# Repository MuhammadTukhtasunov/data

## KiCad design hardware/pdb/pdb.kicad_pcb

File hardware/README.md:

# KiCad projects — Rev A

KiCad projects for the four custom boards in the
[electrical & logic design](../docs/electrical/README.md). Each one has a
complete schematic and a started PCB: board outline, mounting holes, net
classes, ground pours, and every footprint placed and grouped by circuit
block. Nothing is routed yet.

| Board | Folder | Schematic | PCB | Parts | Check results |
|-------|--------|-----------|-----|-------|---------------|
| Power Distribution Board | [`pdb/`](pdb) | [PDF](exports/pdb-schematic.pdf) (A2) | 100 × 80 mm, 4 layers · [PDF](exports/pdb-pcb.pdf) | 94 | 0 DRC violations, 189 unrouted connections |
| Jetson I/O HAT | [`hat/`](hat) | [PDF](exports/hat-schematic.pdf) (A3) | 65 × 56.5 mm, 2 layers · [PDF](exports/hat-pcb.pdf) | 38 | 0 DRC violations, 79 unrouted connections |
| Lighting Driver Board | [`lgt/`](lgt) | [PDF](exports/lgt-schematic.pdf) (A3) | 70 × 50 mm, 2 layers · [PDF](exports/lgt-pcb.pdf) | 35 | 0 DRC violations, 62 unrouted connections |
| Sensor Hub | [`sns/`](sns) | [PDF](exports/sns-schematic.pdf) (A2) | 90 × 60 mm, 2 layers · [PDF](exports/sns-pcb.pdf) | 47 | 0 DRC violations, 104 unrouted connections |

## 3D

| PDB | HAT |
|-----|-----|
|  |  |
| **LGT** | **SNS** |
|  |  |

Exported from KiCad with its 3D model library by
[`tools/export_3d.py`](tools/export_3d.py); top views are in `exports/*-3d-top.png`.
KiCad 7's library has no models for the XT60/XT30, Micro-Fit and JST-SH
connectors or the BVR shunt, so those show as plain boxes sized from their
footprints; a few chips and inductors use the closest library model. The board
files keep their original model references. In KiCad, open *View → 3D Viewer*.

## Previews

| Board | PCB (placement, unrouted) | Schematic |
|-------|---------------------------|-----------|
| PDB |  |  |
| HAT |  |  |
| LGT |  |  |
| SNS |  |  |

In the PCB images, blue is the ground fill, pink is pads and yellow is
silkscreen. Every part sits inside its outline as a starting arrangement, grouped
by circuit block; expect to rearrange them for routing.

Open the `.kicad_pro` file in **KiCad 7 or newer**. KiCad 8 and 9 upgrade the
files the first time you save.

## What's done

- **Schematics** use KiCad's standard symbols, plus a project symbol for the
  Teensy 4.1 in [`lib/drone.kicad_sym`](lib/drone.kicad_sym). Each block from
  the design doc is a labelled frame on one sheet. Every pin connects through a
  net label: global labels for nets that cross boards, using the names in
  the design doc's §3. Unused pins have no-connect flags.
- **Every pin was checked against KiCad's own netlist** (exported with
  `kicad-cli`): each pin is on the net the design intends, and no net has a
  single connection.
- **PCBs** were built from that netlist, so *Update PCB from Schematic* starts
  in sync. Every part is packed inside the outline, and each schematic block
  is a PCB group so you can select its parts together.
- **Net classes** (in each `.kicad_pro`):
  - `HighCurrent`: 3 mm track, for `PWR_VBAT` and `VBAT_RAW`.
  - `Power`: 1 mm track, for `PWR_*`, switch nodes, LED and speaker outputs, and sensor 5 V.
  - `Default`: 0.25 mm track.
  - Minimum drill is 0.2 mm, which the TI PowerPAD thermal-via footprints need.
- **Ground pours** are on `B.Cu` (and `In1.Cu` on the 4-layer PDB).
- **HAT layout:** the 40-pin socket sits along the top edge between the
  mounting holes, as on a Raspberry Pi HAT.

## Before layout: values and checks still open

Values marked **TBD** in the schematics need calculating from datasheets.
I couldn't download datasheets in the session that generated these files.

| Board | Parts | What to do |
|-------|-------|------------|
| PDB | R10–R16, C10–C13 | LM5176: EN/UVLO divider, MODE, RT (switching frequency), SLOPE, SS, compensation, FB divider for 19 V |
| PDB | L1, R17, R18, Q1–Q4 | LM5176 power stage: inductor, low-side current-sense resistor, optional output-sense resistor (0 Ω if unused), confirm CSD18540Q5B suits the chosen frequency |
| PDB | R21–R24, C23–C24, R28–R31, C31–C32, L2, L3 | TPS54560B: EN/UVLO divider, RT, compensation, inductors |
| PDB | R25/R26, R32/R33 | 52.3 k / 10 k assumes a 0.8 V feedback reference; confirm |
| PDB | J1, J2, J3 | Confirm pad 1 is + on the AMASS XT60/XT30 footprints |
| HAT | R1 (634 k) | MAX98357A SD_MODE level for (L+R)/2 mono; check the datasheet's SD_MODE table |
| HAT | U2 | Symbol is 74LVC125 (same pinout); fit a **74AHCT125** |
| LGT | R5, R11, L1, L2 | LED current (≈ 0.1 V / R) and inductor value for your emitters |
| LGT | R3/R4, R9/R10 | AL8860 CTRL voltage range and internal pull-up |
| SNS | U1 | Teensy pin numbers use DIP-48 numbering; check against the PJRC Teensy 4.1 pinout card |

Also choose the battery and motor current (shunt R1, XT60 vs XT90), and pick
final part numbers for the inductors and capacitors.

## Folder layout

```
hardware/
├── lib/drone.kicad_sym      project symbols (Teensy 4.1)
├── pdb/ hat/ lgt/ sns/      one KiCad project each (.kicad_pro, .kicad_sch, .kicad_pcb, sym-lib-table)
├── exports/                 schematic and PCB PDFs
└── tools/                   generator that bootstrapped the projects
```

## Regenerating (bootstrap only)

`tools/gen_kicad.py` holds each board's circuit as a parts-and-nets list and
writes all of the above. **It overwrites the KiCad files.** Once you start
editing in KiCad, edit the KiCad files directly and stop using the script.

It needs KiCad 7's Python module (`pcbnew`), `kiutils==1.4.8` and
`rectpack==0.2.2`:

```bash
python3 -m venv --system-site-packages .venv   # system Python that has pcbnew
.venv/bin/pip install kiutils==1.4.8 rectpack==0.2.2
.venv/bin/python hardware/tools/gen_kicad.py          # all boards
.venv/bin/python hardware/tools/gen_kicad.py lgt      # one board
```

`tools/export_3d.py <kicad 3dmodels dir> <out dir>` exports each board to VRML
with its component models (used for the 3D renders above).

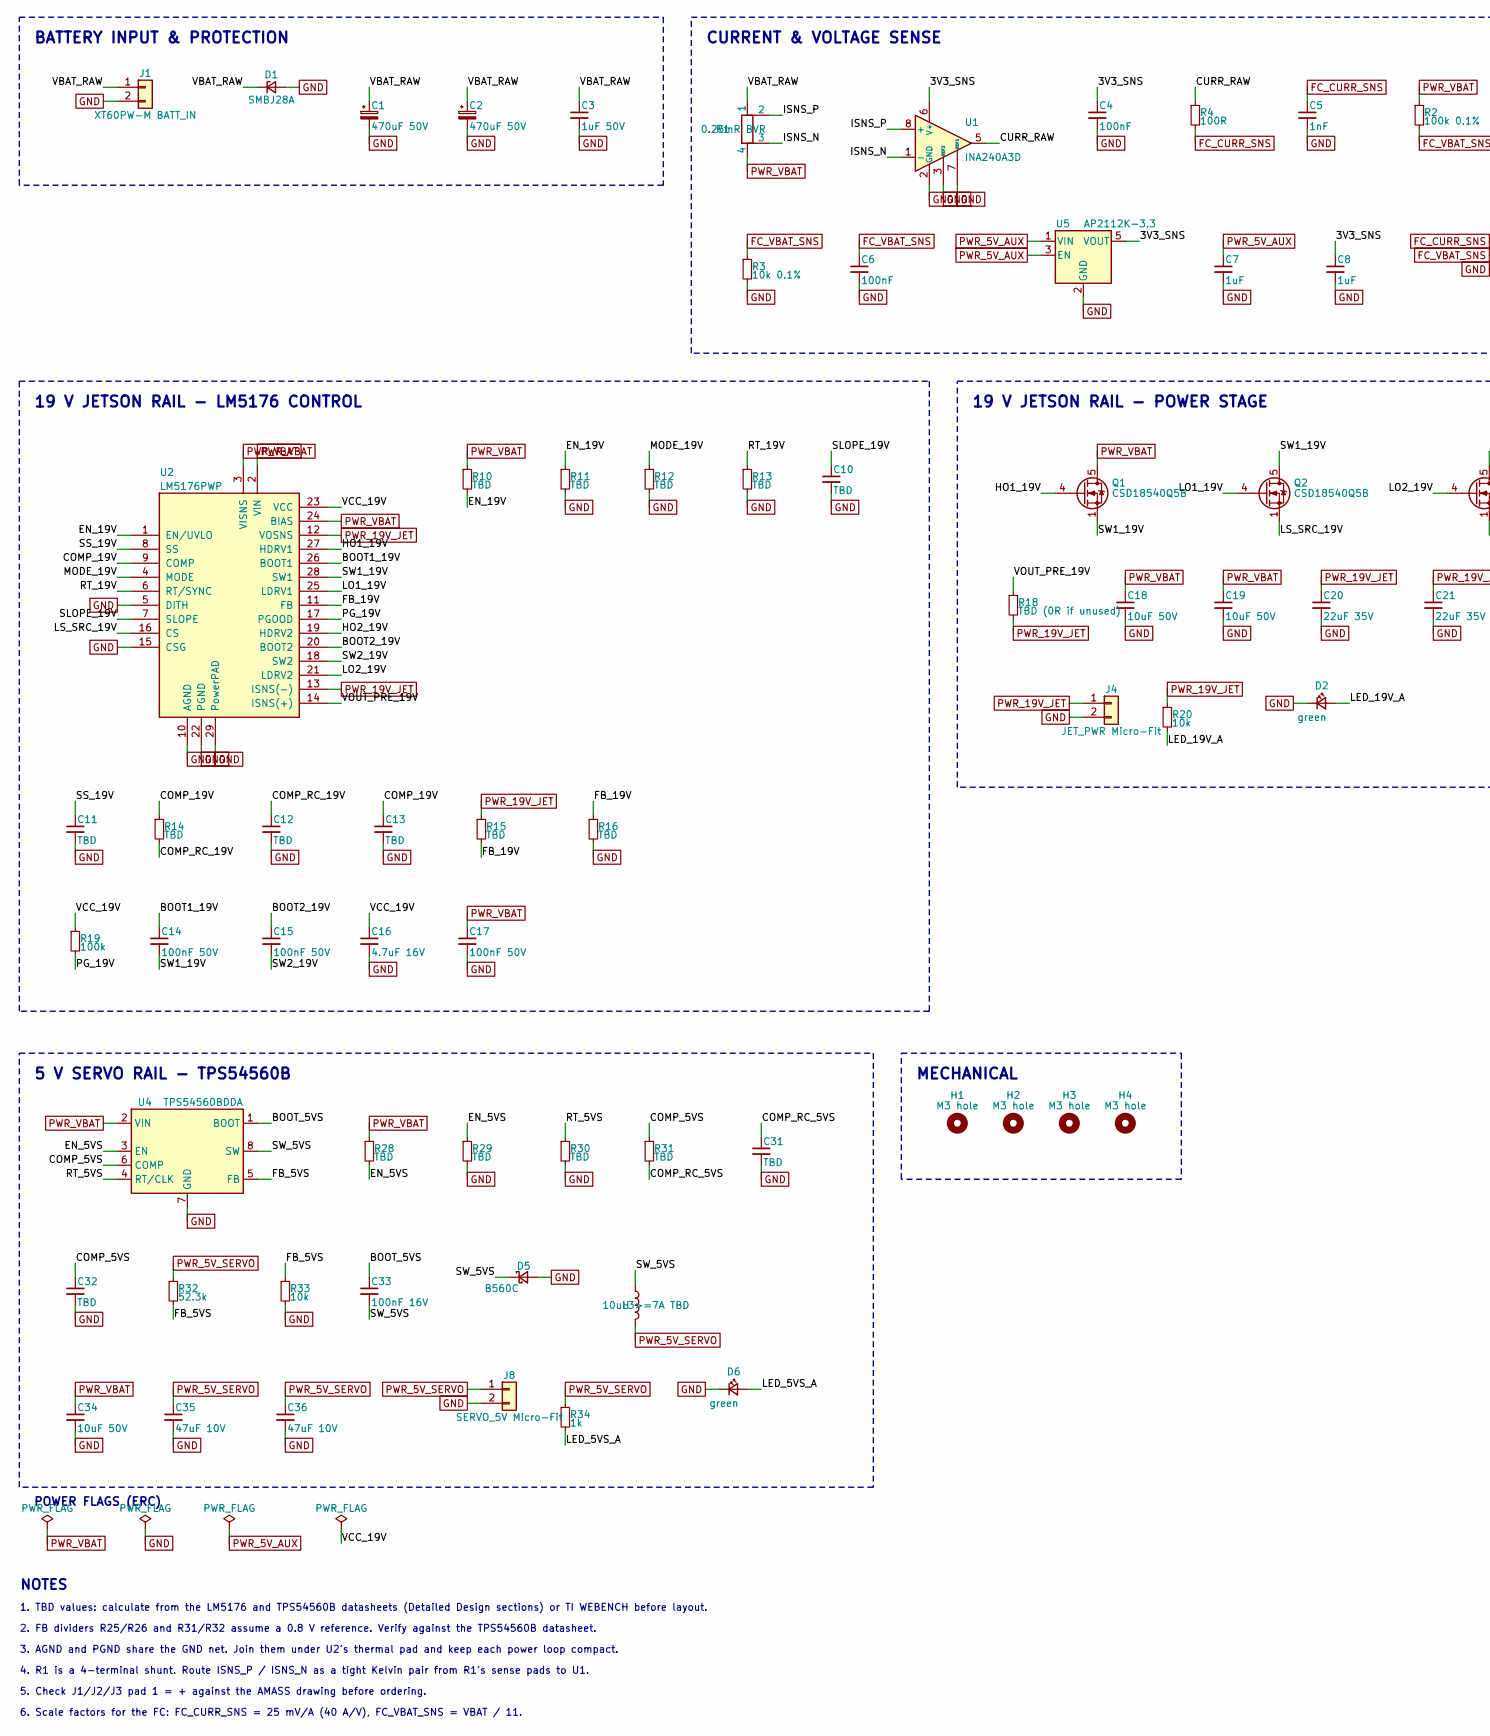
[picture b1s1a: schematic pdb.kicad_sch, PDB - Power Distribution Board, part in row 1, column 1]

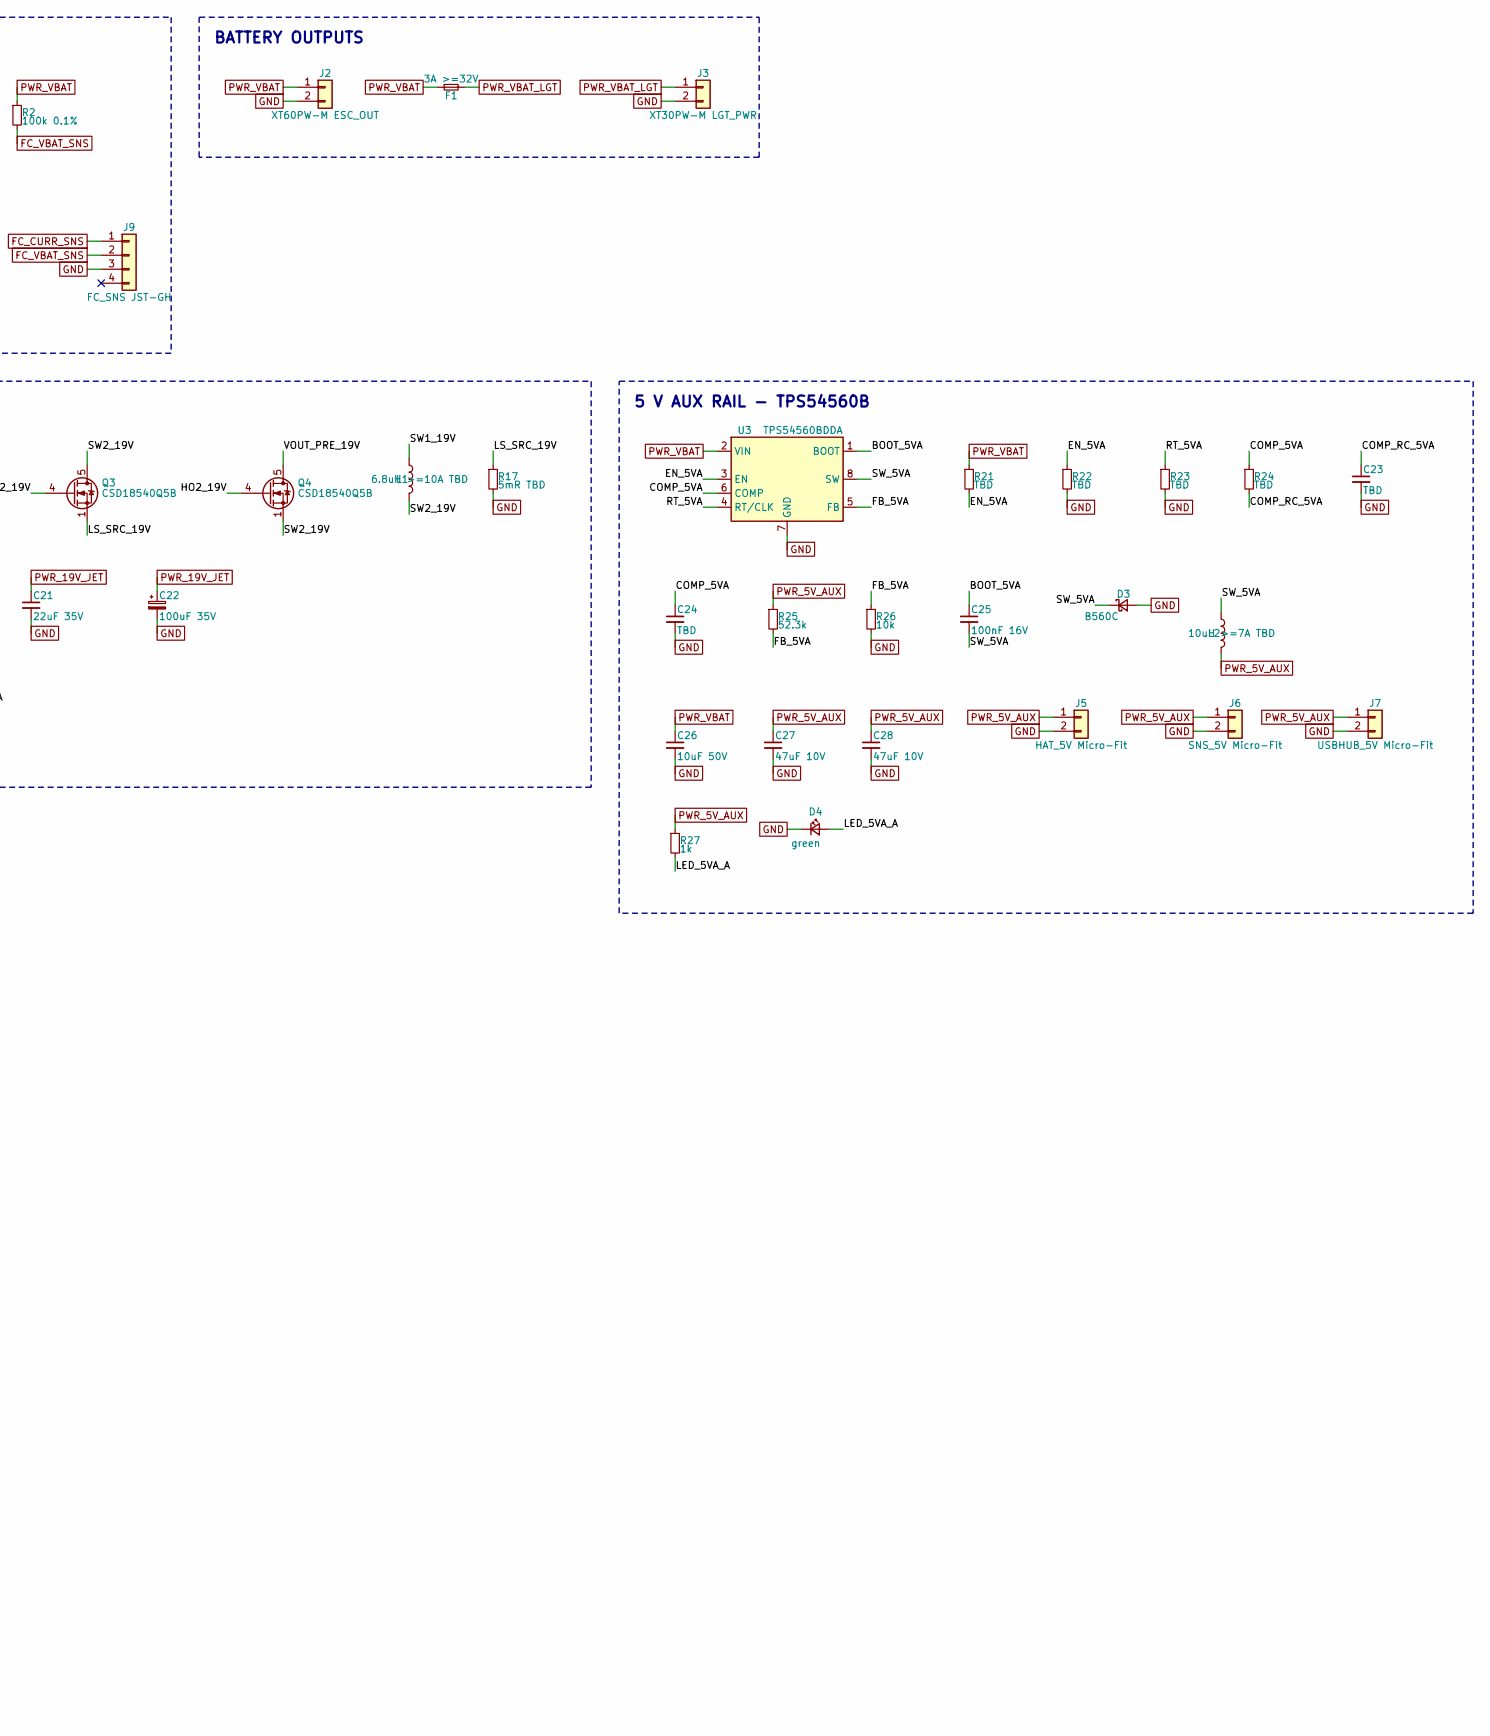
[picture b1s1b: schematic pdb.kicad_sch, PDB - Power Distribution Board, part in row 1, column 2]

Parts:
C1, C2: 470uF 50V; CP_Elec_10x10.5
C3: 1uF 50V; C_1206_3216Metric
C4, C6: 100nF; C_0603_1608Metric
C5: 1nF; C_0603_1608Metric
C7, C8: 1uF; C_0603_1608Metric
C10, C11, C12, C13, C23, C24, C31, C32: TBD; C_0603_1608Metric
C14, C15, C17: 100nF 50V; C_0603_1608Metric
C16: 4.7uF 16V; C_0805_2012Metric
C18, C19, C26, C34: 10uF 50V; C_1210_3225Metric
C20, C21: 22uF 35V; C_1210_3225Metric
C22: 100uF 35V; CP_Elec_8x10.5
C25, C33: 100nF 16V; C_0603_1608Metric
C27, C28, C35, C36: 47uF 10V; C_1210_3225Metric
D1: SMBJ28A; D_SMB
D2, D4, D6: green; LED_0603_1608Metric
D3, D5: B560C; D_SMC
F1: 3A >=32V; Fuse_1206_3216Metric
H1, H2, H3, H4: M3 hole; MountingHole_3.2mm_M3
J1: XT60PW-M BATT_IN; AMASS_XT60PW-M_1x02_P7.20mm_Horizontal
J2: XT60PW-M ESC_OUT; AMASS_XT60PW-M_1x02_P7.20mm_Horizontal
J3: XT30PW-M LGT_PWR; AMASS_XT30PW-M_1x02_P2.50mm_Horizontal
J4: JET_PWR Micro-Fit; Molex_Micro-Fit_3.0_43650-0210_1x02-1MP_P3.00mm_Horizontal
J5: HAT_5V Micro-Fit; Molex_Micro-Fit_3.0_43650-0210_1x02-1MP_P3.00mm_Horizontal
J6: SNS_5V Micro-Fit; Molex_Micro-Fit_3.0_43650-0210_1x02-1MP_P3.00mm_Horizontal
J7: USBHUB_5V Micro-Fit; Molex_Micro-Fit_3.0_43650-0210_1x02-1MP_P3.00mm_Horizontal
J8: SERVO_5V Micro-Fit; Molex_Micro-Fit_3.0_43650-0210_1x02-1MP_P3.00mm_Horizontal
J9: FC_SNS JST-GH; JST_GH_SM04B-GHS-TB_1x04-1MP_P1.25mm_Horizontal
L1: 6.8uH >=10A TBD; L_Bourns_SRP1245A
L2, L3: 10uH >=7A TBD; L_Bourns_SRP1245A
Q1, Q2, Q3, Q4: CSD18540Q5B; TDSON-8-1
R1: 0.25mR BVR; R_Shunt_Isabellenhuette_BVR4026
R2: 100k 0.1%; R_0603_1608Metric
R3: 10k 0.1%; R_0603_1608Metric
R4: 100R; R_0603_1608Metric
R10, R11, R12, R13, R14, R15, R16, R21, R22, R23, R24, R28, R29, R30, R31: TBD; R_0603_1608Metric
R17: 5mR TBD; R_2512_6332Metric
R18: TBD (0R if unused); R_2512_6332Metric
R19: 100k; R_0603_1608Metric
R20, R26, R33: 10k; R_0603_1608Metric
R25, R32: 52.3k; R_0603_1608Metric
R27, R34: 1k; R_0603_1608Metric
U1: INA240A3D; SOIC-8_3.9x4.9mm_P1.27mm
U2: LM5176PWP; HTSSOP-28-1EP_4.4x9.7mm_P0.65mm_EP3.4x9.5mm_ThermalVias
U3, U4: TPS54560BDDA; Texas_R-PDSO-G8_EP2.95x4.9mm_Mask2.4x3.1mm_ThermalVias
U5: AP2112K-3.3; SOT-23-5

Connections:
3V3_SNS: C4.1, C8.1, U1.6 (V+), U5.5 (VOUT)
BOOT1_19V: C14.1, U2.26 (BOOT1)
BOOT2_19V: C15.1, U2.20 (BOOT2)
BOOT_5VA: C25.1, U3.1 (BOOT)
BOOT_5VS: C33.1, U4.1 (BOOT)
COMP_5VA: C24.1, R24.1, U3.6 (COMP)
COMP_5VS: C32.1, R31.1, U4.6 (COMP)
COMP_19V: C13.1, R14.1, U2.9 (COMP)
COMP_RC_5VA: C23.1, R24.2
COMP_RC_5VS: C31.1, R31.2
COMP_RC_19V: C12.1, R14.2
CURR_RAW: R4.1, U1.5
EN_5VA: R21.2, R22.1, U3.3 (EN)
EN_5VS: R28.2, R29.1, U4.3 (EN)
EN_19V: R10.2, R11.1, U2.1 (EN/UVLO)
FB_5VA: R25.2, R26.1, U3.5 (FB)
FB_5VS: R32.2, R33.1, U4.5 (FB)
FB_19V: R15.2, R16.1, U2.11 (FB)
FC_CURR_SNS: C5.1, J9.1, R4.2
FC_VBAT_SNS: C6.1, J9.2, R2.2, R3.1
GND: C1.2, C2.2, C3.2, C4.2, C5.2, C6.2, C7.2, C8.2, C10.2, C11.2, C12.2, C13.2, C16.2, C17.2, C18.2, C19.2, C20.2, C21.2, C22.2, C23.2, C24.2, C26.2, C27.2, C28.2, C31.2, C32.2, C34.2, C35.2, C36.2, D1.2 (A), D2.1 (K), D3.2 (A), D4.1 (K), D5.2 (A), D6.1 (K), J1.2, J2.2, J3.2, J4.2, J5.2, J6.2, J7.2, J8.2, J9.3, R3.2, R11.2, R12.2, R13.2, R16.2, R17.2, R22.2, R23.2, R26.2, R29.2, R30.2, R33.2, U1.2 (GND), U1.3 (REF2), U1.4 (GND), U1.7 (REF1), U2.5 (DITH), U2.10 (AGND), U2.15 (CSG), U2.22 (PGND), U2.29 (PowerPAD), U3.7 (GND), U3.9 (GND), U4.7 (GND), U4.9 (GND), U5.2 (GND)
HO1_19V: Q1.4 (G), U2.27 (HDRV1)
HO2_19V: Q4.4 (G), U2.19 (HDRV2)
ISNS_N: R1.3, U1.1 (-)
ISNS_P: R1.2, U1.8 (+)
LED_5VA_A: D4.2 (A), R27.2
LED_5VS_A: D6.2 (A), R34.2
LED_19V_A: D2.2 (A), R20.2
LO1_19V: Q2.4 (G), U2.25 (LDRV1)
LO2_19V: Q3.4 (G), U2.21 (LDRV2)
LS_SRC_19V: Q2.1 (S), Q2.2 (S), Q2.3 (S), Q3.1 (S), Q3.2 (S), Q3.3 (S), R17.1, U2.16 (CS)
MODE_19V: R12.1, U2.4 (MODE)
PG_19V: R19.2, U2.17 (PGOOD)
PWR_5V_AUX: C7.1, C27.1, C28.1, J5.1, J6.1, J7.1, L2.2, R25.1, R27.1, U5.1 (VIN), U5.3 (EN)
PWR_5V_SERVO: C35.1, C36.1, J8.1, L3.2, R32.1, R34.1
PWR_19V_JET: C20.1, C21.1, C22.1, J4.1, R15.1, R18.2, R20.1, U2.12 (VOSNS), U2.13 (ISNS(-))
PWR_VBAT: C17.1, C18.1, C19.1, C26.1, C34.1, F1.1, J2.1, Q1.5 (D), R1.4, R2.1, R10.1, R21.1, R28.1, U2.2 (VIN), U2.3 (VISNS), U2.24 (BIAS), U3.2 (VIN), U4.2 (VIN)
PWR_VBAT_LGT: F1.2, J3.1
RT_5VA: R23.1, U3.4 (RT/CLK)
RT_5VS: R30.1, U4.4 (RT/CLK)
RT_19V: R13.1, U2.6 (RT/SYNC)
SLOPE_19V: C10.1, U2.7 (SLOPE)
SS_19V: C11.1, U2.8 (SS)
SW1_19V: C14.2, L1.1, Q1.1 (S), Q1.2 (S), Q1.3 (S), Q2.5 (D), U2.28 (SW1)
SW2_19V: C15.2, L1.2, Q3.5 (D), Q4.1 (S), Q4.2 (S), Q4.3 (S), U2.18 (SW2)
SW_5VA: C25.2, D3.1 (K), L2.1, U3.8 (SW)
SW_5VS: C33.2, D5.1 (K), L3.1, U4.8 (SW)
VBAT_RAW: C1.1, C2.1, C3.1, D1.1 (K), J1.1, R1.1
VCC_19V: C16.1, R19.1, U2.23 (VCC)
VOUT_PRE_19V: Q4.5 (D), R18.1, U2.14 (ISNS(+))

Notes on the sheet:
BATTERY INPUT & PROTECTION
CURRENT & VOLTAGE SENSE
BATTERY OUTPUTS
19 V JETSON RAIL - LM5176 CONTROL
19 V JETSON RAIL - POWER STAGE
5 V AUX RAIL - TPS54560B
5 V SERVO RAIL - TPS54560B
MECHANICAL
POWER FLAGS (ERC)
NOTES
1. TBD values: calculate from the LM5176 and TPS54560B datasheets (Detailed Design sections) or TI WEBENCH before layout.
2. FB dividers R25/R26 and R31/R32 assume a 0.8 V reference. Verify against the TPS54560B datasheet.
3. AGND and PGND share the GND net. Join them under U2's thermal pad and keep each power loop compact.
4. R1 is a 4-terminal shunt. Route ISNS_P / ISNS_N as a tight Kelvin pair from R1's sense pads to U1.
5. Check J1/J2/J3 pad 1 = + against the AMASS drawing before ordering.
6. Scale factors for the FC: FC_CURR_SNS = 25 mV/A (40 A/V), FC_VBAT_SNS = VBAT / 11.

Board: 4 copper layers, 94 parts (0 on the bottom side), 50 nets, no tracks yet.

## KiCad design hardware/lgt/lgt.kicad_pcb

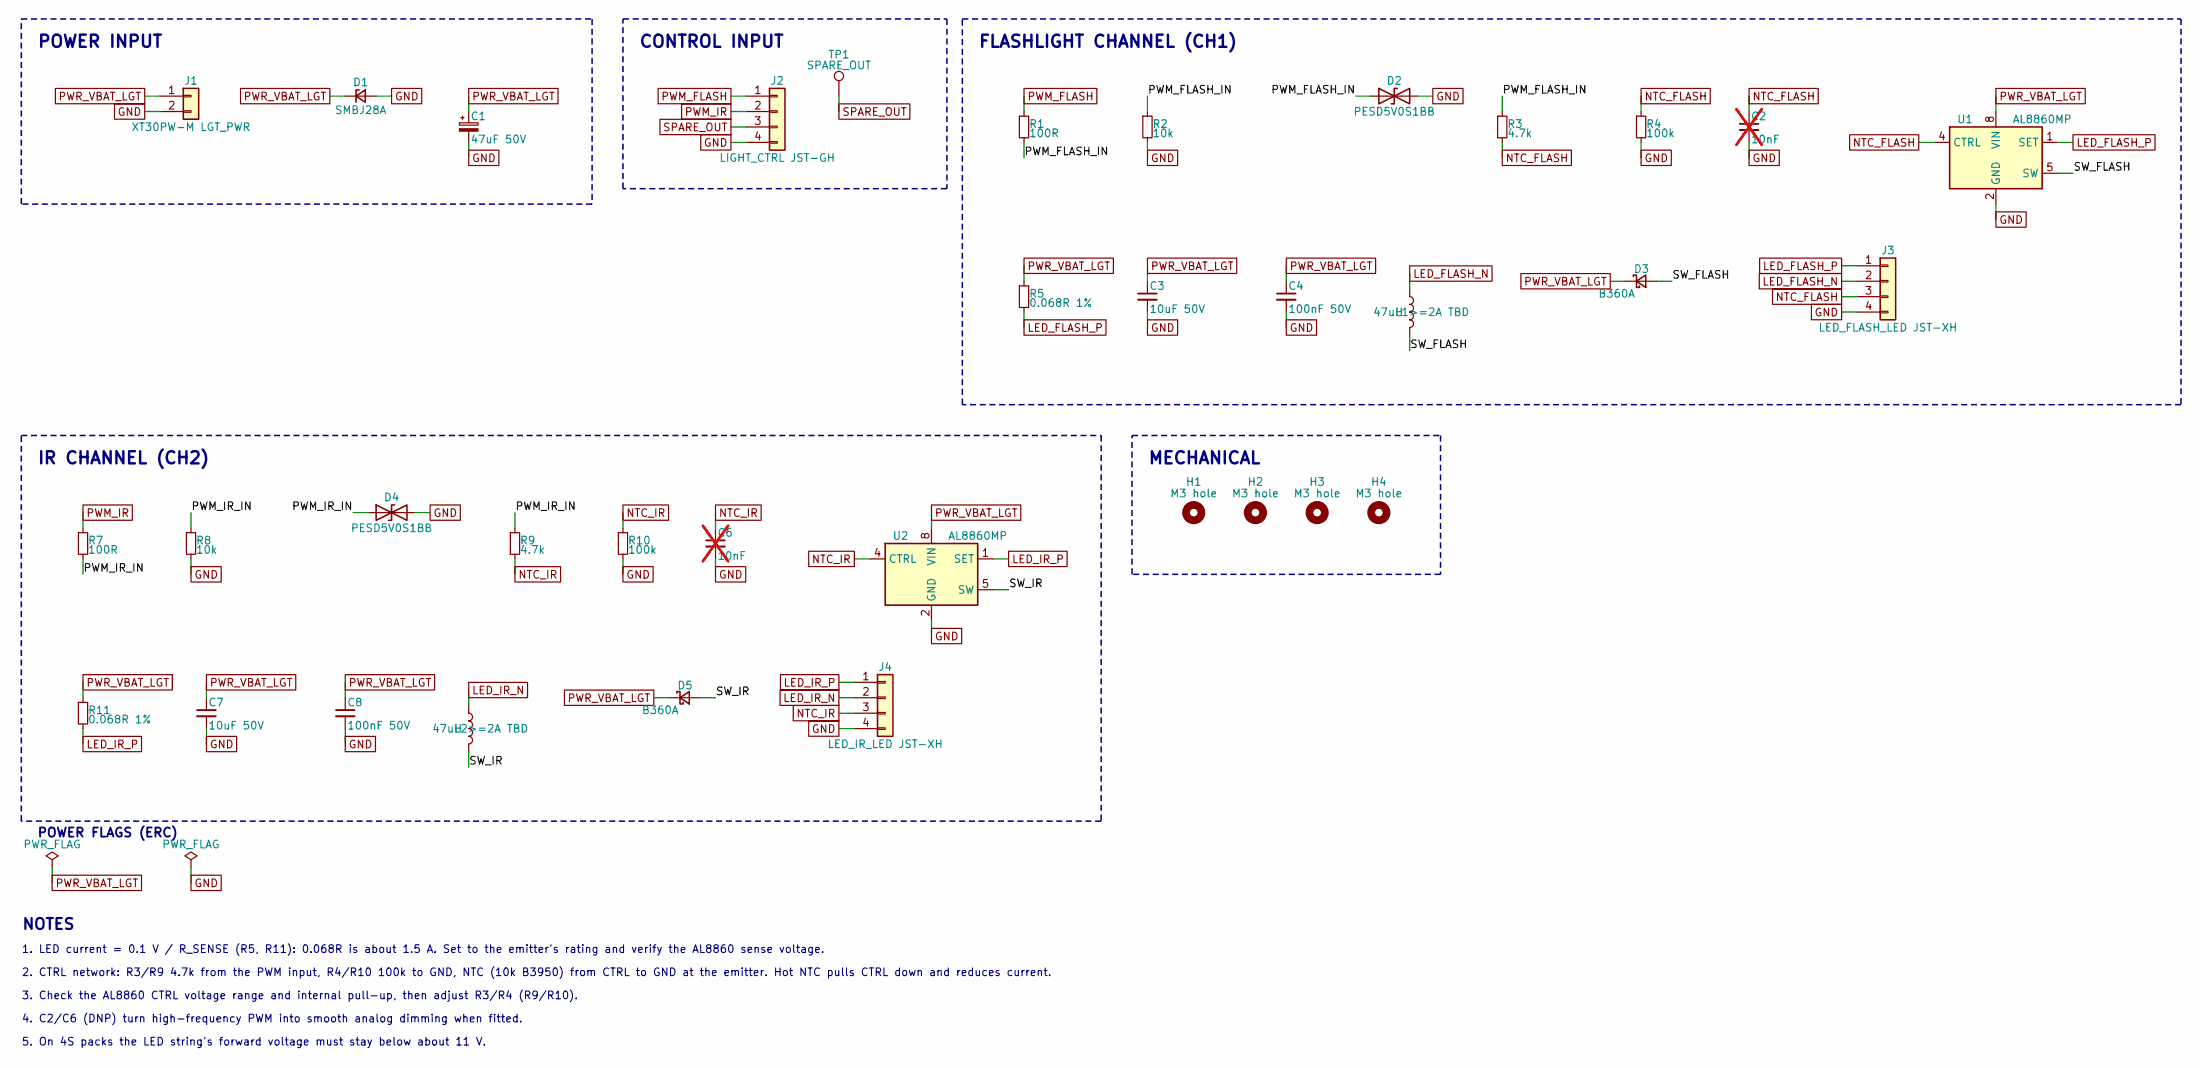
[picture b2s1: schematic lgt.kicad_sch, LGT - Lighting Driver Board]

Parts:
C1: 47uF 50V; CP_Elec_8x10.5
C2, C6: 10nF; C_0603_1608Metric; not fitted
C3, C7: 10uF 50V; C_1210_3225Metric
C4, C8: 100nF 50V; C_0603_1608Metric
D1: SMBJ28A; D_SMB
D2, D4: PESD5V0S1BB; D_SOD-323
D3, D5: B360A; D_SMA
H1, H2, H3, H4: M3 hole; MountingHole_3.2mm_M3
J1: XT30PW-M LGT_PWR; AMASS_XT30PW-M_1x02_P2.50mm_Horizontal
J2: LIGHT_CTRL JST-GH; JST_GH_SM04B-GHS-TB_1x04-1MP_P1.25mm_Horizontal
J3: LED_FLASH_LED JST-XH; JST_XH_B4B-XH-A_1x04_P2.50mm_Vertical
J4: LED_IR_LED JST-XH; JST_XH_B4B-XH-A_1x04_P2.50mm_Vertical
L1, L2: 47uH >=2A TBD; L_12x12mm_H6mm
R1, R7: 100R; R_0603_1608Metric
R2, R8: 10k; R_0603_1608Metric
R3, R9: 4.7k; R_0603_1608Metric
R4, R10: 100k; R_0603_1608Metric
R5, R11: 0.068R 1%; R_1206_3216Metric
TP1: SPARE_OUT; TestPoint_Pad_D1.5mm
U1, U2: AL8860MP; MSOP-8-1EP_3x3mm_P0.65mm_EP1.5x1.8mm

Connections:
GND: C1.2, C2.2, C3.2, C4.2, C6.2, C7.2, C8.2, D1.2 (A), D2.2 (A2), D4.2 (A2), J1.2, J2.4, J3.4, J4.4, R2.2, R4.2, R8.2, R10.2, U1.2 (GND), U1.3 (GND), U1.9 (GND), U2.2 (GND), U2.3 (GND), U2.9 (GND)
LED_FLASH_N: J3.2, L1.1
LED_FLASH_P: J3.1, R5.2, U1.1 (SET)
LED_IR_N: J4.2, L2.1
LED_IR_P: J4.1, R11.2, U2.1 (SET)
NTC_FLASH: C2.1, J3.3, R3.2, R4.1, U1.4 (CTRL)
NTC_IR: C6.1, J4.3, R9.2, R10.1, U2.4 (CTRL)
PWM_FLASH: J2.1, R1.1
PWM_FLASH_IN: D2.1 (A1), R1.2, R2.1, R3.1
PWM_IR: J2.2, R7.1
PWM_IR_IN: D4.1 (A1), R7.2, R8.1, R9.1
PWR_VBAT_LGT: C1.1, C3.1, C4.1, C7.1, C8.1, D1.1 (K), D3.1 (K), D5.1 (K), J1.1, R5.1, R11.1, U1.8 (VIN), U2.8 (VIN)
SPARE_OUT: J2.3, TP1.1
SW_FLASH: D3.2 (A), L1.2, U1.5 (SW), U1.6 (SW)
SW_IR: D5.2 (A), L2.2, U2.5 (SW), U2.6 (SW)

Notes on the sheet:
POWER INPUT
CONTROL INPUT
FLASHLIGHT CHANNEL (CH1)
IR CHANNEL (CH2)
MECHANICAL
POWER FLAGS (ERC)
NOTES
1. LED current = 0.1 V / R_SENSE (R5, R11): 0.068R is about 1.5 A. Set to the emitter's rating and verify the AL8860 sense voltage.
2. CTRL network: R3/R9 4.7k from the PWM input, R4/R10 100k to GND, NTC (10k B3950) from CTRL to GND at the emitter. Hot NTC pulls CTRL down and reduces current.
3. Check the AL8860 CTRL voltage range and internal pull-up, then adjust R3/R4 (R9/R10).
4. C2/C6 (DNP) turn high-frequency PWM into smooth analog dimming when fitted.
5. On 4S packs the LED string's forward voltage must stay below about 11 V.

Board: 2 copper layers, 35 parts (0 on the bottom side), 15 nets, no tracks yet.

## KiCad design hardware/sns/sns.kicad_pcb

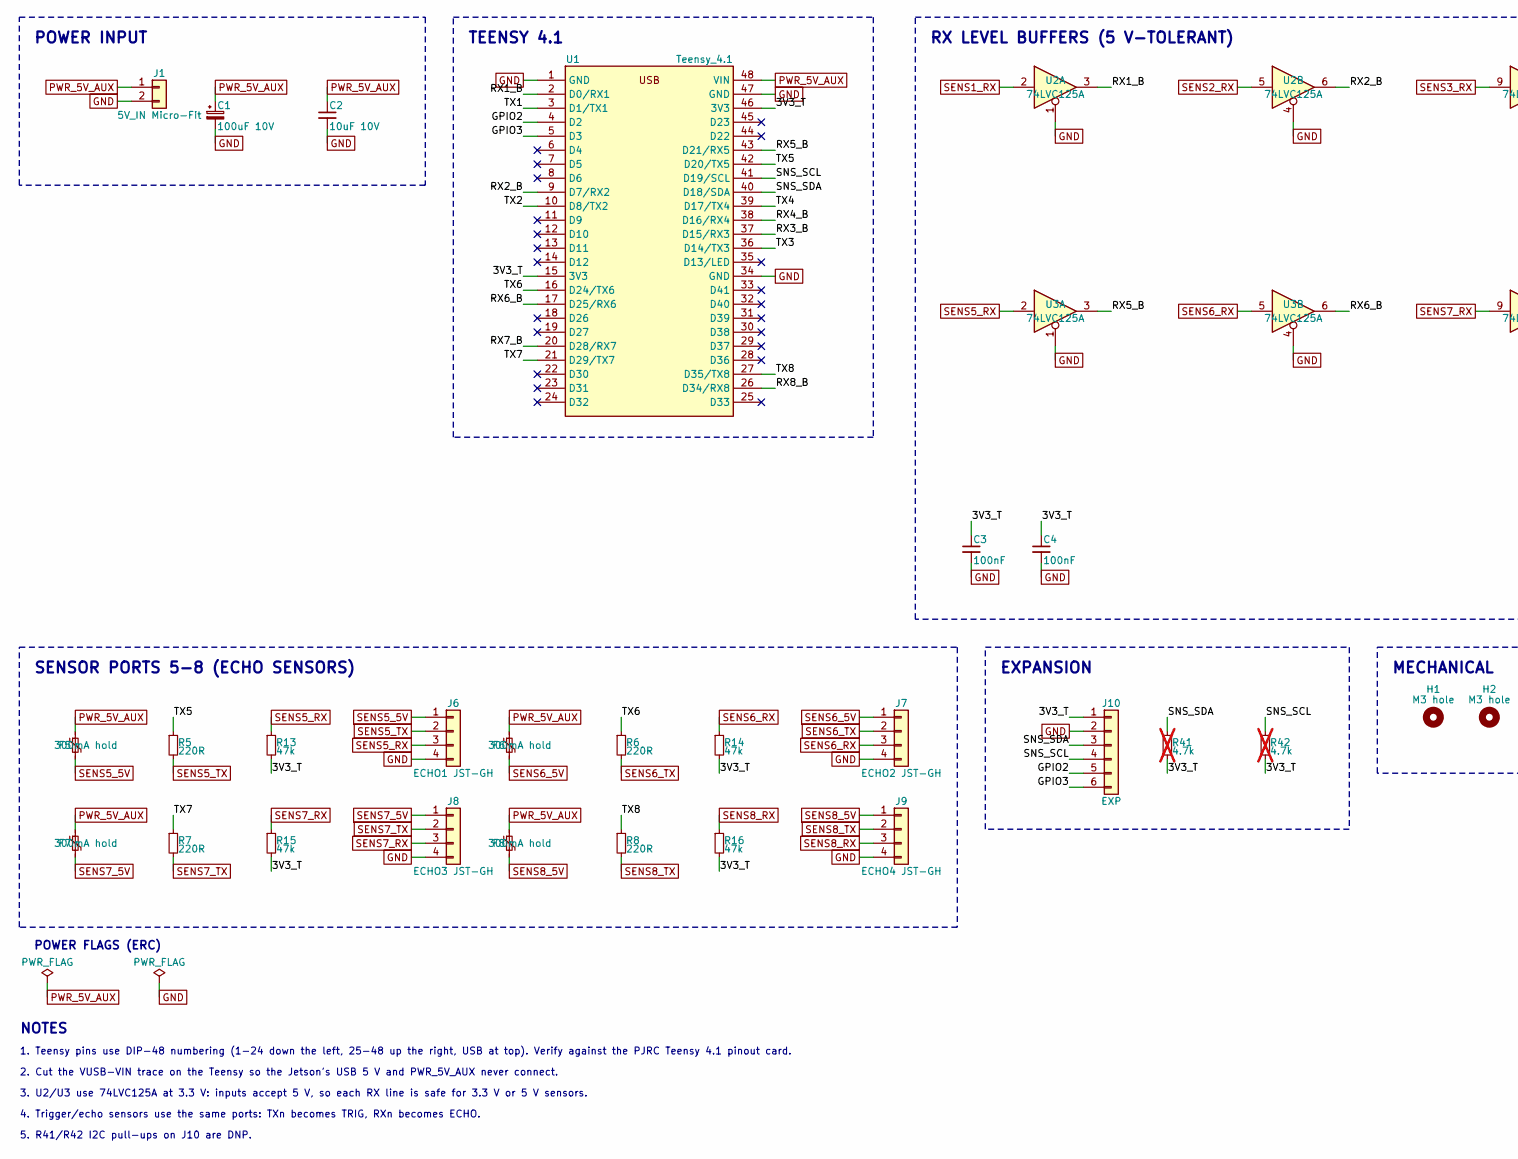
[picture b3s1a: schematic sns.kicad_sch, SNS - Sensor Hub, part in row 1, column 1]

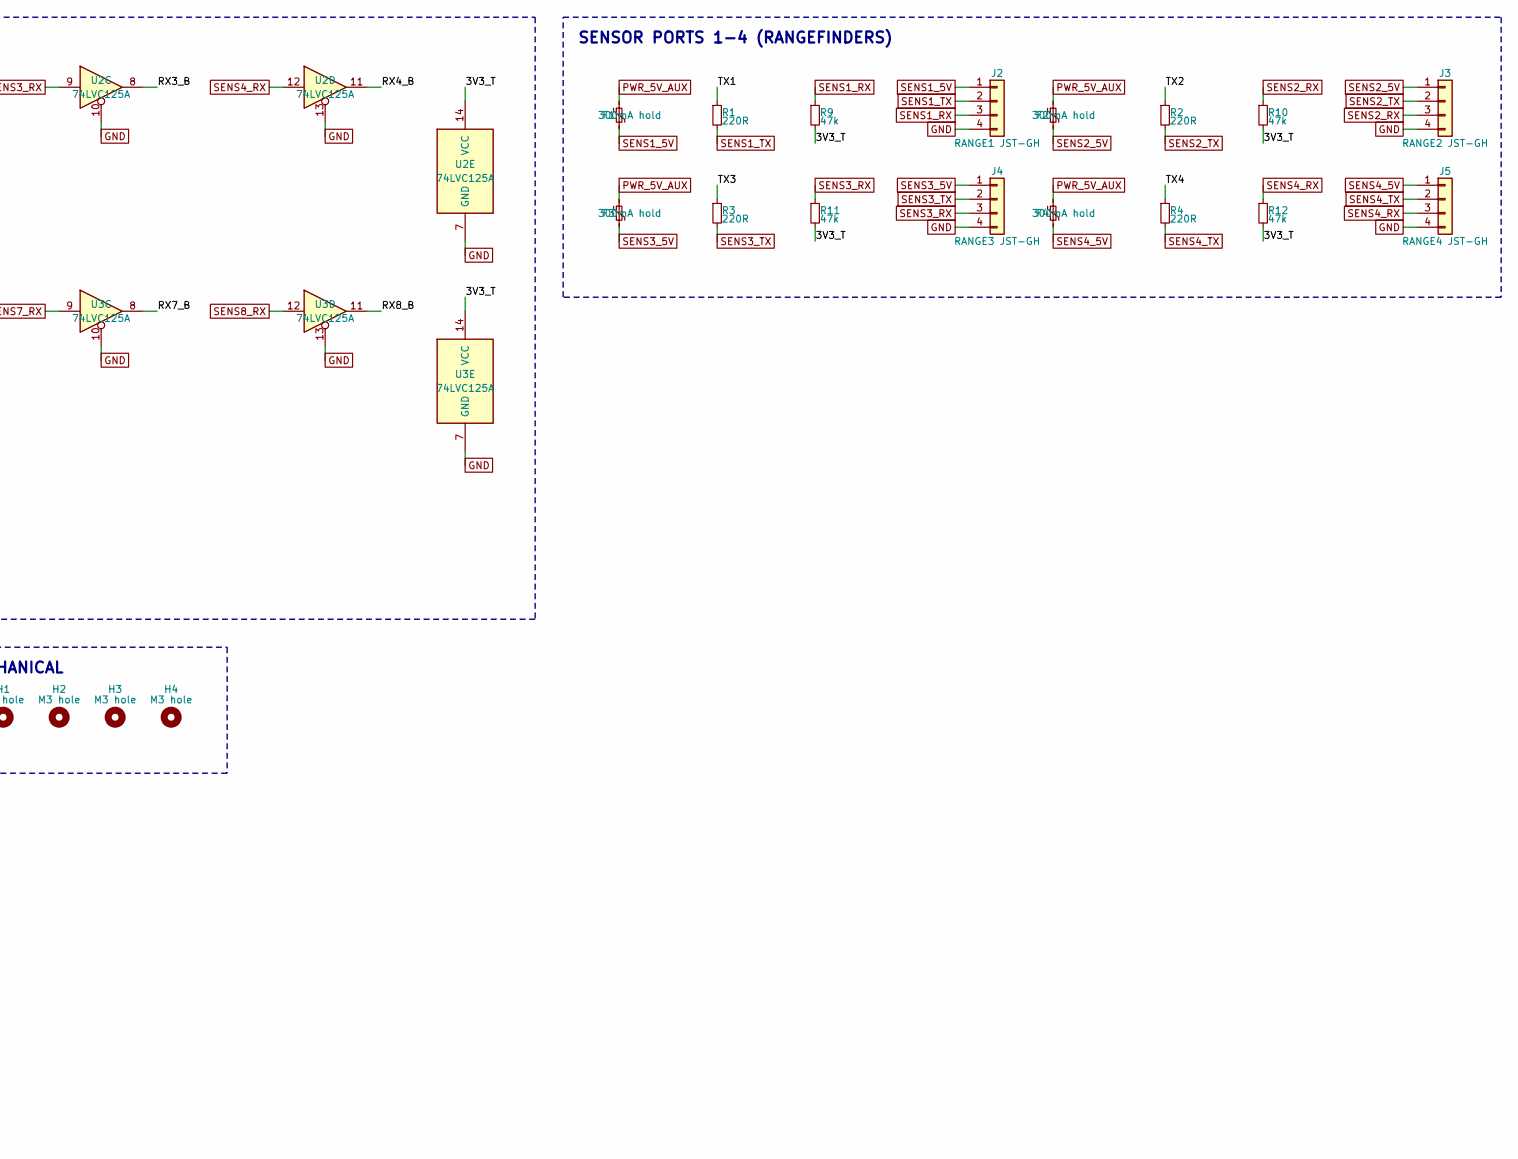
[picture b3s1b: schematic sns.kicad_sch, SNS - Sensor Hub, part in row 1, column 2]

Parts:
C1: 100uF 10V; CP_Elec_8x10.5
C2: 10uF 10V; C_0805_2012Metric
C3, C4: 100nF; C_0603_1608Metric
F1, F2, F3, F4, F5, F6, F7, F8: 300mA hold; Fuse_1206_3216Metric
H1, H2, H3, H4: M3 hole; MountingHole_3.2mm_M3
J1: 5V_IN Micro-Fit; Molex_Micro-Fit_3.0_43650-0210_1x02-1MP_P3.00mm_Horizontal
J2: RANGE1 JST-GH; JST_GH_SM04B-GHS-TB_1x04-1MP_P1.25mm_Horizontal
J3: RANGE2 JST-GH; JST_GH_SM04B-GHS-TB_1x04-1MP_P1.25mm_Horizontal
J4: RANGE3 JST-GH; JST_GH_SM04B-GHS-TB_1x04-1MP_P1.25mm_Horizontal
J5: RANGE4 JST-GH; JST_GH_SM04B-GHS-TB_1x04-1MP_P1.25mm_Horizontal
J6: ECHO1 JST-GH; JST_GH_SM04B-GHS-TB_1x04-1MP_P1.25mm_Horizontal
J7: ECHO2 JST-GH; JST_GH_SM04B-GHS-TB_1x04-1MP_P1.25mm_Horizontal
J8: ECHO3 JST-GH; JST_GH_SM04B-GHS-TB_1x04-1MP_P1.25mm_Horizontal
J9: ECHO4 JST-GH; JST_GH_SM04B-GHS-TB_1x04-1MP_P1.25mm_Horizontal
J10: EXP; PinHeader_1x06_P2.54mm_Vertical
R1, R2, R3, R4, R5, R6, R7, R8: 220R; R_0603_1608Metric
R9, R10, R11, R12, R13, R14, R15, R16: 47k; R_0603_1608Metric
R41, R42: 4.7k; R_0603_1608Metric; not fitted
U1: Teensy_4.1; DIP-48_W15.24mm_Socket
U2, U3: 74LVC125A; SOIC-14_3.9x8.7mm_P1.27mm

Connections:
3V3_T: C3.1, C4.1, J10.1, R9.2, R10.2, R11.2, R12.2, R13.2, R14.2, R15.2, R16.2, R41.2, R42.2, U1.15 (3V3), U1.46 (3V3), U2.14 (VCC), U3.14 (VCC)
GND: C1.2, C2.2, C3.2, C4.2, J1.2, J2.4, J3.4, J4.4, J5.4, J6.4, J7.4, J8.4, J9.4, J10.2, U1.1 (GND), U1.34 (GND), U1.47 (GND), U2.1, U2.4, U2.7 (GND), U2.10, U2.13, U3.1, U3.4, U3.7 (GND), U3.10, U3.13
GPIO2: J10.5, U1.4 (D2)
GPIO3: J10.6, U1.5 (D3)
PWR_5V_AUX: C1.1, C2.1, F1.1, F2.1, F3.1, F4.1, F5.1, F6.1, F7.1, F8.1, J1.1, U1.48 (VIN)
RX1_B: U1.2 (D0/RX1), U2.3
RX2_B: U1.9 (D7/RX2), U2.6
RX3_B: U1.37 (D15/RX3), U2.8
RX4_B: U1.38 (D16/RX4), U2.11
RX5_B: U1.43 (D21/RX5), U3.3
RX6_B: U1.17 (D25/RX6), U3.6
RX7_B: U1.20 (D28/RX7), U3.8
RX8_B: U1.26 (D34/RX8), U3.11
SENS1_5V: F1.2, J2.1
SENS1_RX: J2.3, R9.1, U2.2
SENS1_TX: J2.2, R1.2
SENS2_5V: F2.2, J3.1
SENS2_RX: J3.3, R10.1, U2.5
SENS2_TX: J3.2, R2.2
SENS3_5V: F3.2, J4.1
SENS3_RX: J4.3, R11.1, U2.9
SENS3_TX: J4.2, R3.2
SENS4_5V: F4.2, J5.1
SENS4_RX: J5.3, R12.1, U2.12
SENS4_TX: J5.2, R4.2
SENS5_5V: F5.2, J6.1
SENS5_RX: J6.3, R13.1, U3.2
SENS5_TX: J6.2, R5.2
SENS6_5V: F6.2, J7.1
SENS6_RX: J7.3, R14.1, U3.5
SENS6_TX: J7.2, R6.2
SENS7_5V: F7.2, J8.1
SENS7_RX: J8.3, R15.1, U3.9
SENS7_TX: J8.2, R7.2
SENS8_5V: F8.2, J9.1
SENS8_RX: J9.3, R16.1, U3.12
SENS8_TX: J9.2, R8.2
SNS_SCL: J10.4, R42.1, U1.41 (D19/SCL)
SNS_SDA: J10.3, R41.1, U1.40 (D18/SDA)
TX1: R1.1, U1.3 (D1/TX1)
TX2: R2.1, U1.10 (D8/TX2)
TX3: R3.1, U1.36 (D14/TX3)
TX4: R4.1, U1.39 (D17/TX4)
TX5: R5.1, U1.42 (D20/TX5)
TX6: R6.1, U1.16 (D24/TX6)
TX7: R7.1, U1.21 (D29/TX7)
TX8: R8.1, U1.27 (D35/TX8)

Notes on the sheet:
POWER INPUT
TEENSY 4.1
RX LEVEL BUFFERS (5 V-TOLERANT)
SENSOR PORTS 1-4 (RANGEFINDERS)
SENSOR PORTS 5-8 (ECHO SENSORS)
EXPANSION
MECHANICAL
POWER FLAGS (ERC)
NOTES
1. Teensy pins use DIP-48 numbering (1-24 down the left, 25-48 up the right, USB at top). Verify against the PJRC Teensy 4.1 pinout card.
2. Cut the VUSB-VIN trace on the Teensy so the Jetson's USB 5 V and PWR_5V_AUX never connect.
3. U2/U3 use 74LVC125A at 3.3 V: inputs accept 5 V, so each RX line is safe for 3.3 V or 5 V sensors.
4. Trigger/echo sensors use the same ports: TXn becomes TRIG, RXn becomes ECHO.
5. R41/R42 I2C pull-ups on J10 are DNP.

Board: 2 copper layers, 47 parts (0 on the bottom side), 47 nets, no tracks yet.
